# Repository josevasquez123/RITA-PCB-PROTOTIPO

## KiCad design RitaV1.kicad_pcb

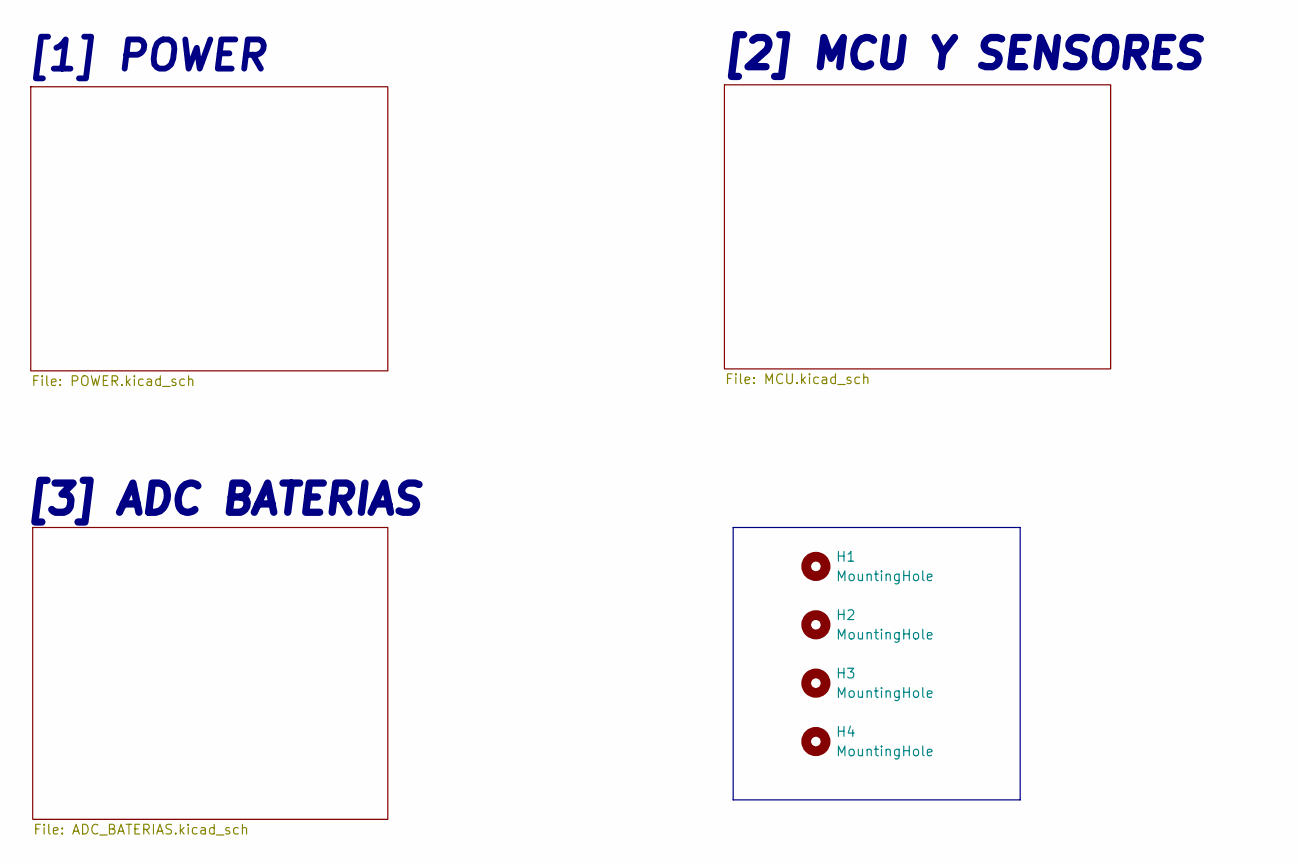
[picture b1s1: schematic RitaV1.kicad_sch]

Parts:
H1, H2, H3, H4: MountingHole; MountingHole_3.2mm_M3

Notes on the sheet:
[1] POWER
[3] ADC BATERIAS
[2] MCU Y SENSORES

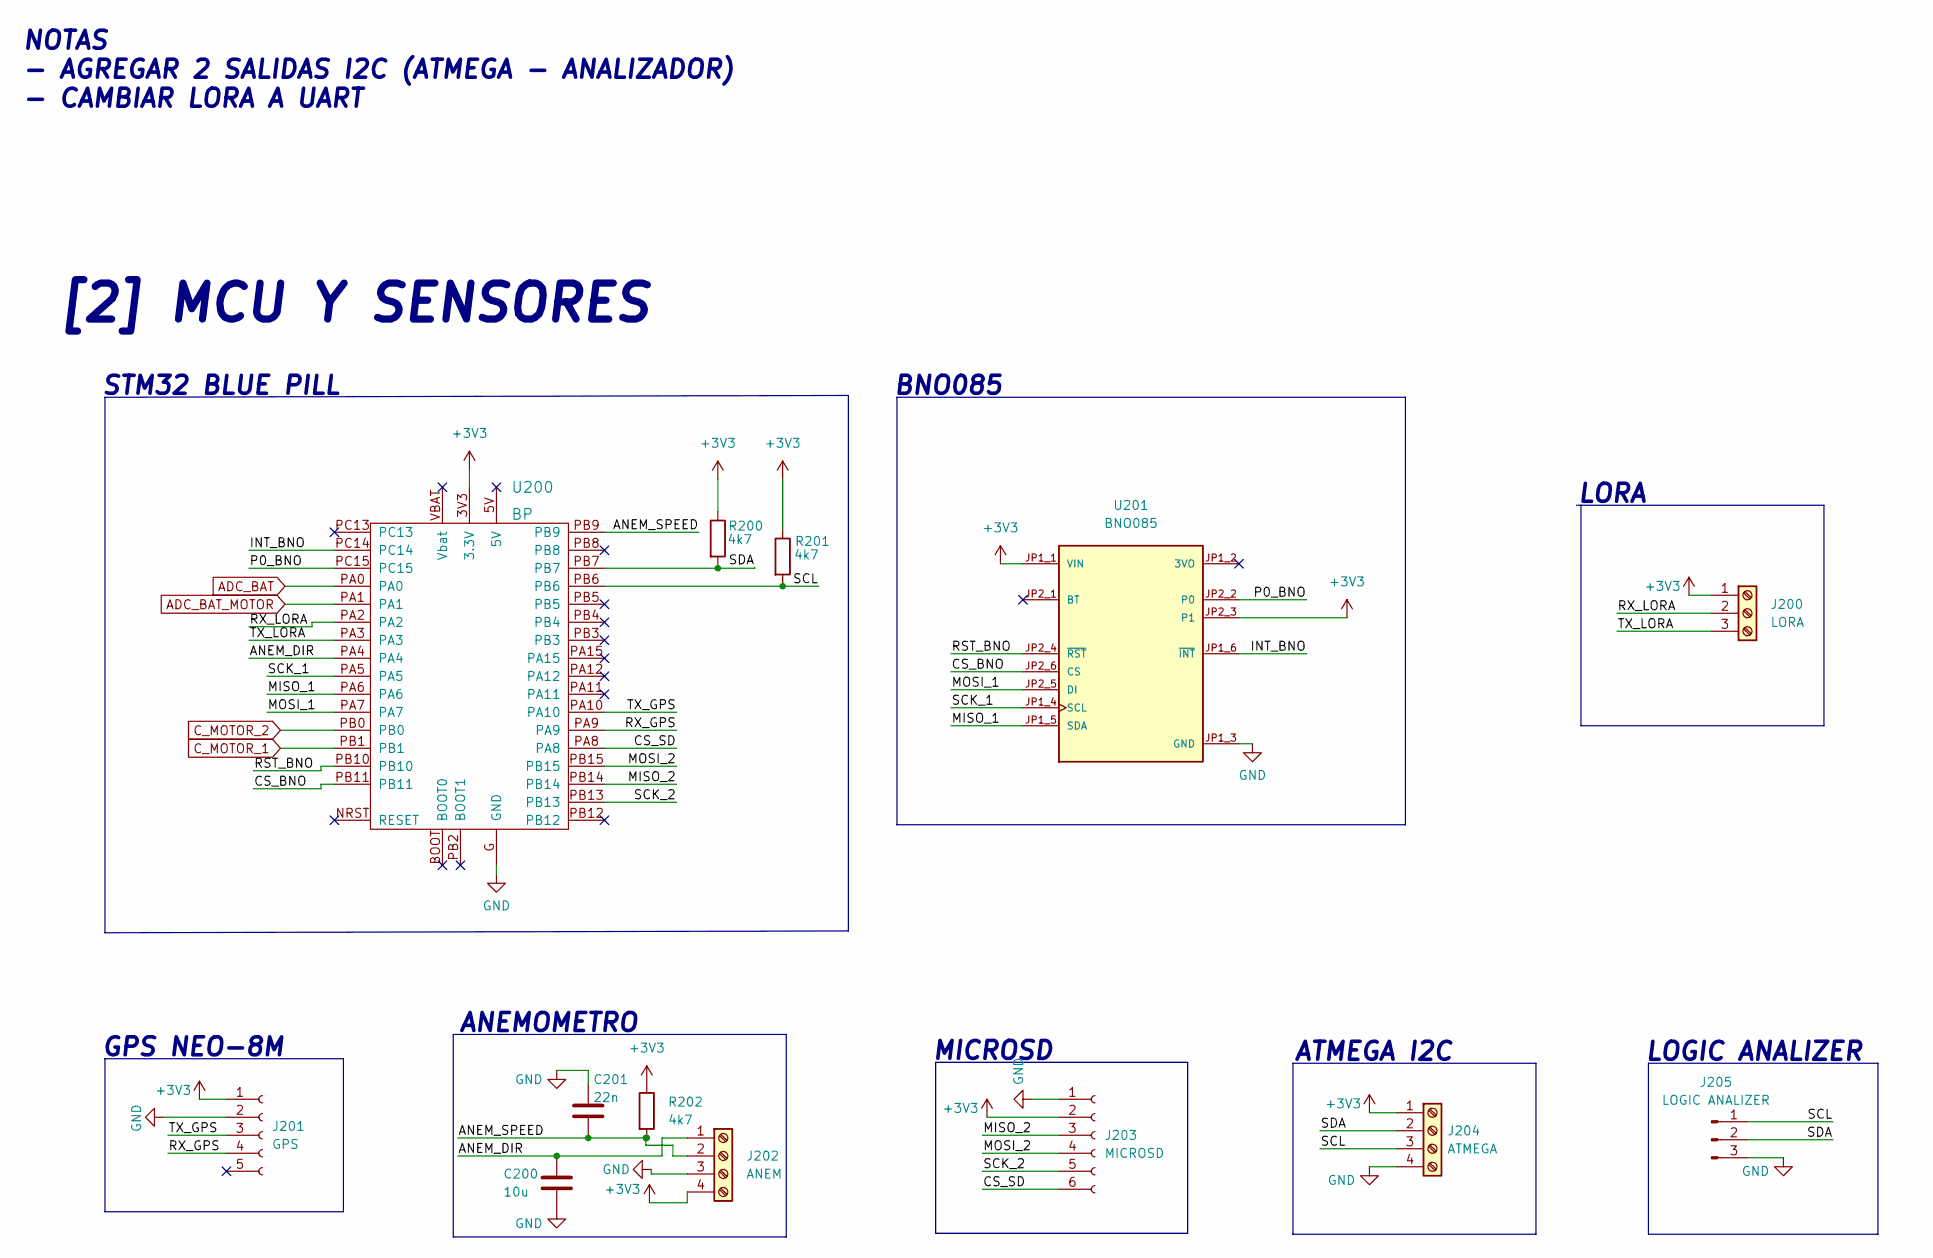
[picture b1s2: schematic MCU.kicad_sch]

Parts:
C200: 10u; C_Radial_D4.0mm_H5.0mm_P1.50mm
C201: 22n; C_Disc_D3.0mm_W1.6mm_P2.50mm
J200: LORA; PhoenixContact_MSTBA_2,5_3-G-5,08_1x03_P5.08mm_Horizontal
J201: GPS; PinSocket_1x05_P2.54mm_Horizontal
J202: ANEM; PhoenixContact_MSTBA_2,5_4-G-5,08_1x04_P5.08mm_Horizontal
J203: MICROSD; PinSocket_1x06_P2.54mm_Horizontal
J204: ATMEGA; PhoenixContact_MSTBA_2,5_4-G-5,08_1x04_P5.08mm_Horizontal
J205: LOGIC ANALIZER; PinHeader_1x03_P2.54mm_Vertical
R200, R201, R202: 4k7; R_Axial_DIN0204_L3.6mm_D1.6mm_P5.08mm_Horizontal
U200: BP; blue_pill
U201: BNO085; MODULE_4754; PARTREV 2021-03-16

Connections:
+3V3: J200.1, J201.1, J202.4, J203.2, J204.1, R200.1, R201.1, R202.1, U200.3V3 (3.3V), U201.JP1_1 (VIN), U201.JP2_3 (P1); also elsewhere on the board
/MCU/ANEM_DIR: C200.1, J202.1, U200.PA4
/MCU/ANEM_SPEED: C201.2, J202.2, R202.2, U200.PB9
/MCU/CS_BNO: U200.PB11, U201.JP2_6 (CS)
/MCU/CS_SD: J203.6, U200.PA8
/MCU/INT_BNO: U200.PC14, U201.JP1_6 (~INT)
/MCU/MISO_1: U200.PA6, U201.JP1_5 (SDA)
/MCU/MISO_2: J203.3, U200.PB14
/MCU/MOSI_1: U200.PA7, U201.JP2_5 (DI)
/MCU/MOSI_2: J203.4, U200.PB15
/MCU/P0_BNO: U200.PC15, U201.JP2_2 (P0)
/MCU/RST_BNO: U200.PB10, U201.JP2_4 (~RST)
/MCU/RX_GPS: J201.4, U200.PA9
/MCU/RX_LORA: J200.2, U200.PA2
/MCU/SCK_1: U200.PA5, U201.JP1_4 (SCL)
/MCU/SCK_2: J203.5, U200.PB13
/MCU/SCL: J204.3, J205.1, R201.2, U200.PB6
/MCU/SDA: J204.2, J205.2, R200.2, U200.PB7
/MCU/TX_GPS: J201.3, U200.PA10
/MCU/TX_LORA: J200.3, U200.PA3
ADC_BAT: U200.PA0; also elsewhere on the board
ADC_BAT_MOTOR: U200.PA1; also elsewhere on the board
C_MOTOR_1: U200.PB1; also elsewhere on the board
C_MOTOR_2: U200.PB0; also elsewhere on the board
GND: C200.2, C201.1, J201.2, J202.3, J203.1, J204.4, J205.3, U200.G (GND), U201.JP1_3 (GND); also elsewhere on the board

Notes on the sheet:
GPS NEO-8M
MICROSD
BNO085
LOGIC ANALIZER
LORA
ATMEGA I2C
STM32 BLUE PILL
[2] MCU Y SENSORES
NOTAS - AGREGAR 2 SALIDAS I2C (ATMEGA - ANALIZADOR) - CAMBIAR LORA A UART
ANEMOMETRO

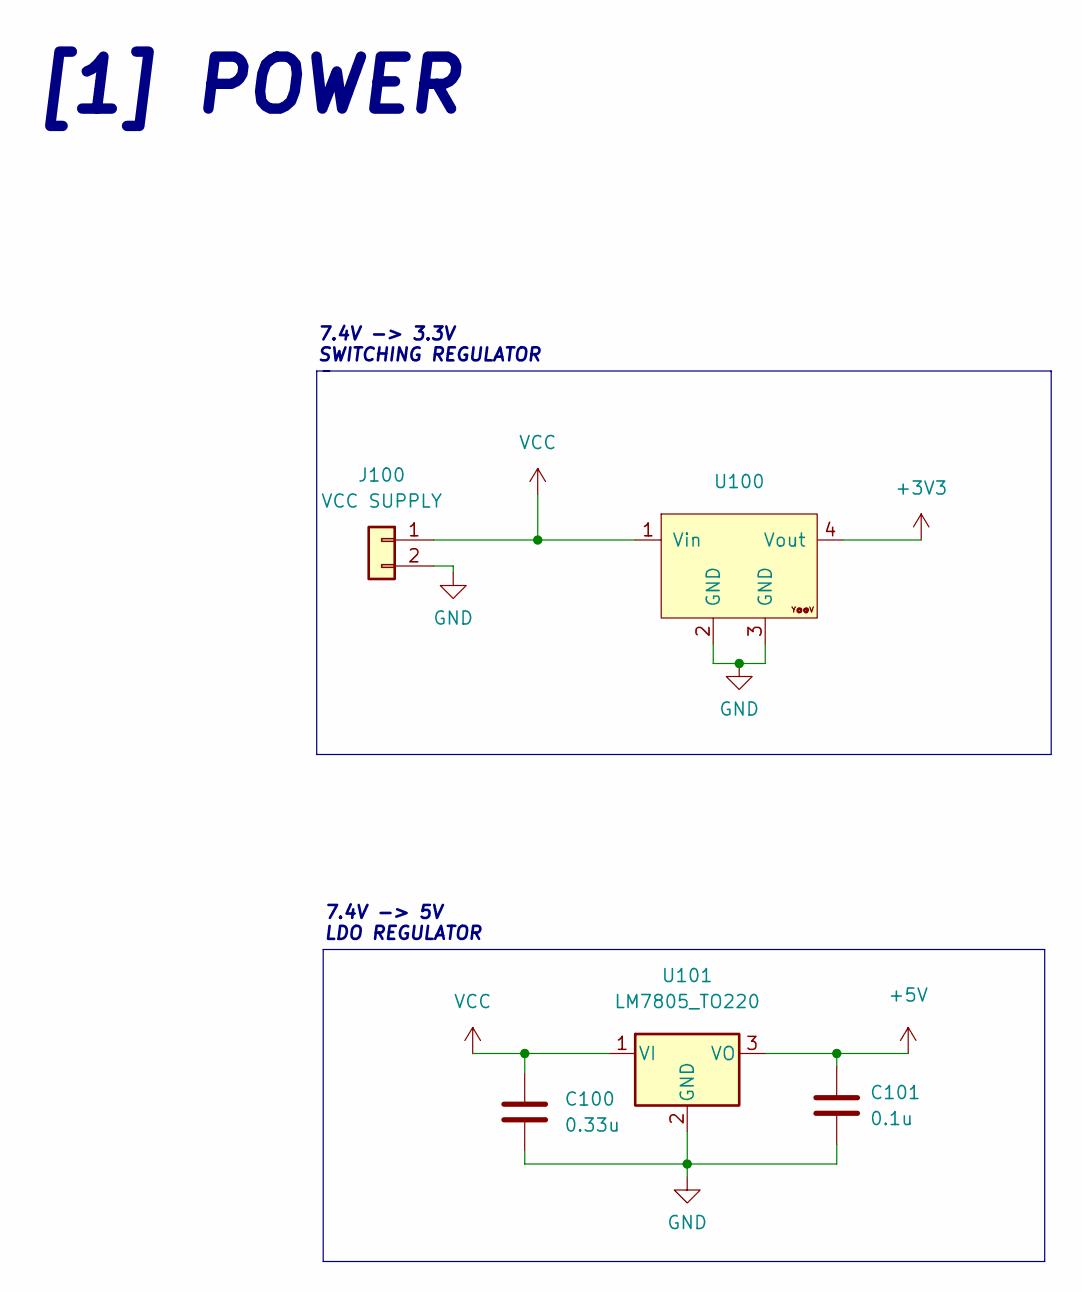
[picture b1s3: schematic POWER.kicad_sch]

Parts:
C100: 0.33u; C_Disc_D3.0mm_W1.6mm_P2.50mm
C101: 0.1u; C_Disc_D3.0mm_W1.6mm_P2.50mm
J100: VCC SUPPLY; PhoenixContact_MSTBA_2,5_2-G-5,08_1x02_P5.08mm_Horizontal
U100: YAAJ_DCDC_StepDown_LM2596
U101: LM7805_TO220; TO-220-3_Vertical

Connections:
+3V3: U100.4 (Vout); also elsewhere on the board
+5V: C101.1, U101.3 (VO); also elsewhere on the board
GND: C100.2, C101.2, J100.2, U100.2 (GND), U100.3 (GND), U101.2 (GND); also elsewhere on the board
VCC: C100.1, J100.1, U100.1 (Vin), U101.1 (VI); also elsewhere on the board

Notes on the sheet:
[1] POWER
7.4V -> 5V LDO REGULATOR
7.4V -> 3.3V SWITCHING REGULATOR

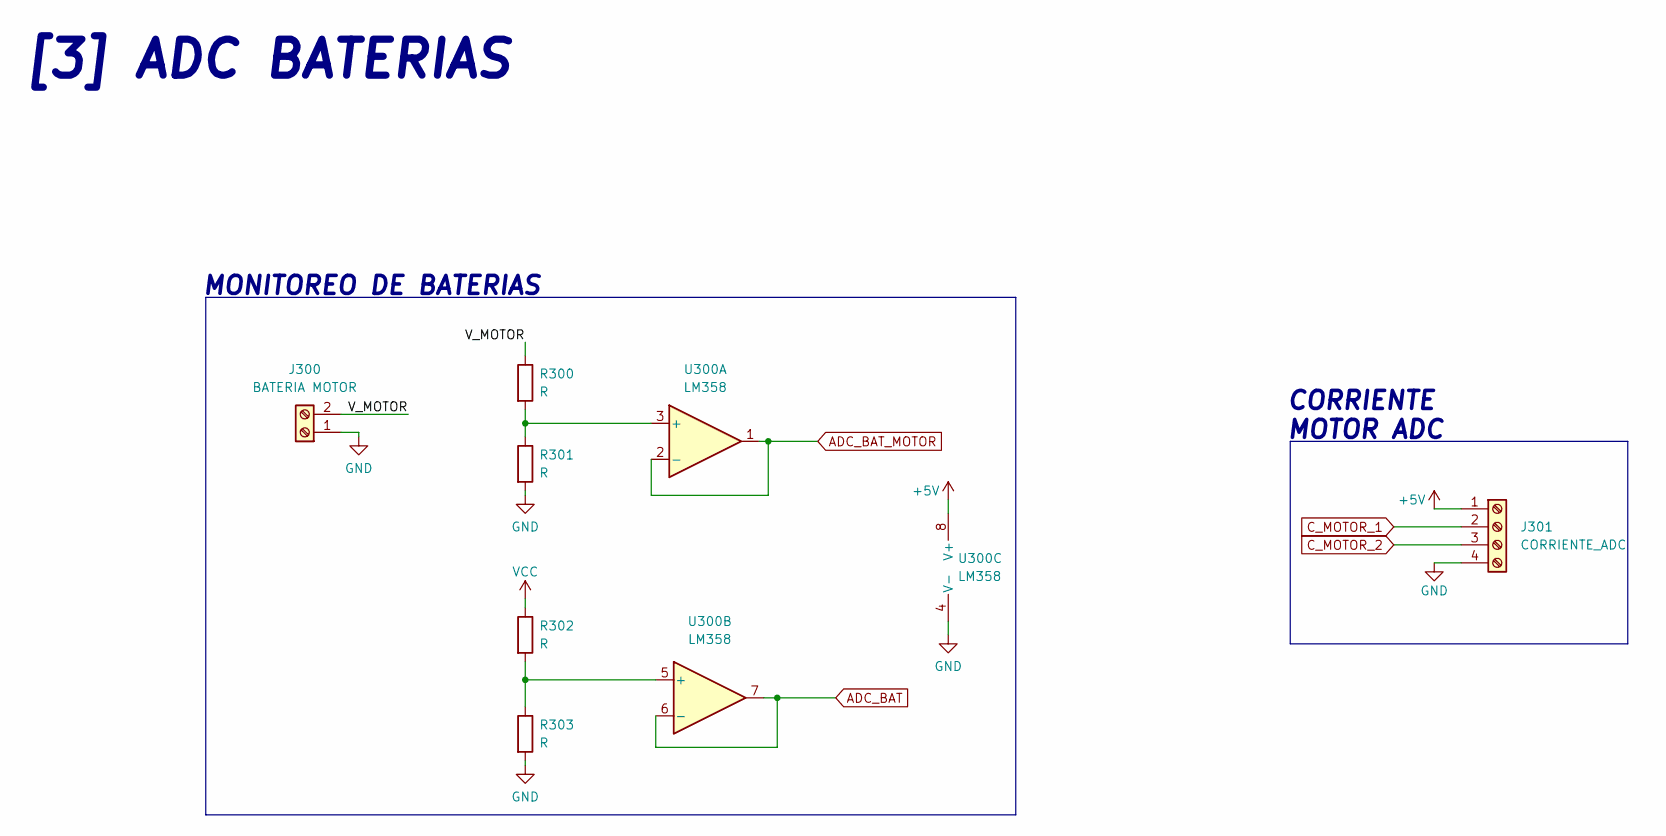
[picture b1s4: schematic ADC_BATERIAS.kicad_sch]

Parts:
J300: BATERIA MOTOR; PhoenixContact_MSTBA_2,5_2-G-5,08_1x02_P5.08mm_Horizontal
J301: CORRIENTE_ADC; PhoenixContact_MSTBA_2,5_4-G-5,08_1x04_P5.08mm_Horizontal
R300, R301, R302, R303: R; R_Axial_DIN0204_L3.6mm_D1.6mm_P5.08mm_Horizontal
U300: LM358; DIP-8_W7.62mm

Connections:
+5V: J301.1, U300.8 (V+); also elsewhere on the board
/ADC_BATERIAS/V_MOTOR: J300.2, R300.1
ADC_BAT: U300.6 (-), U300.7; also elsewhere on the board
ADC_BAT_MOTOR: U300.1, U300.2 (-); also elsewhere on the board
C_MOTOR_1: J301.2; also elsewhere on the board
C_MOTOR_2: J301.3; also elsewhere on the board
GND: J300.1, J301.4, R301.2, R303.2, U300.4 (V-); also elsewhere on the board
unnamed: R300.2, R301.1, U300.3 (+)
unnamed: R302.2, R303.1, U300.5 (+)
VCC: R302.1; also elsewhere on the board

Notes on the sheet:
MONITOREO DE BATERIAS
CORRIENTE MOTOR ADC
[3] ADC BATERIAS

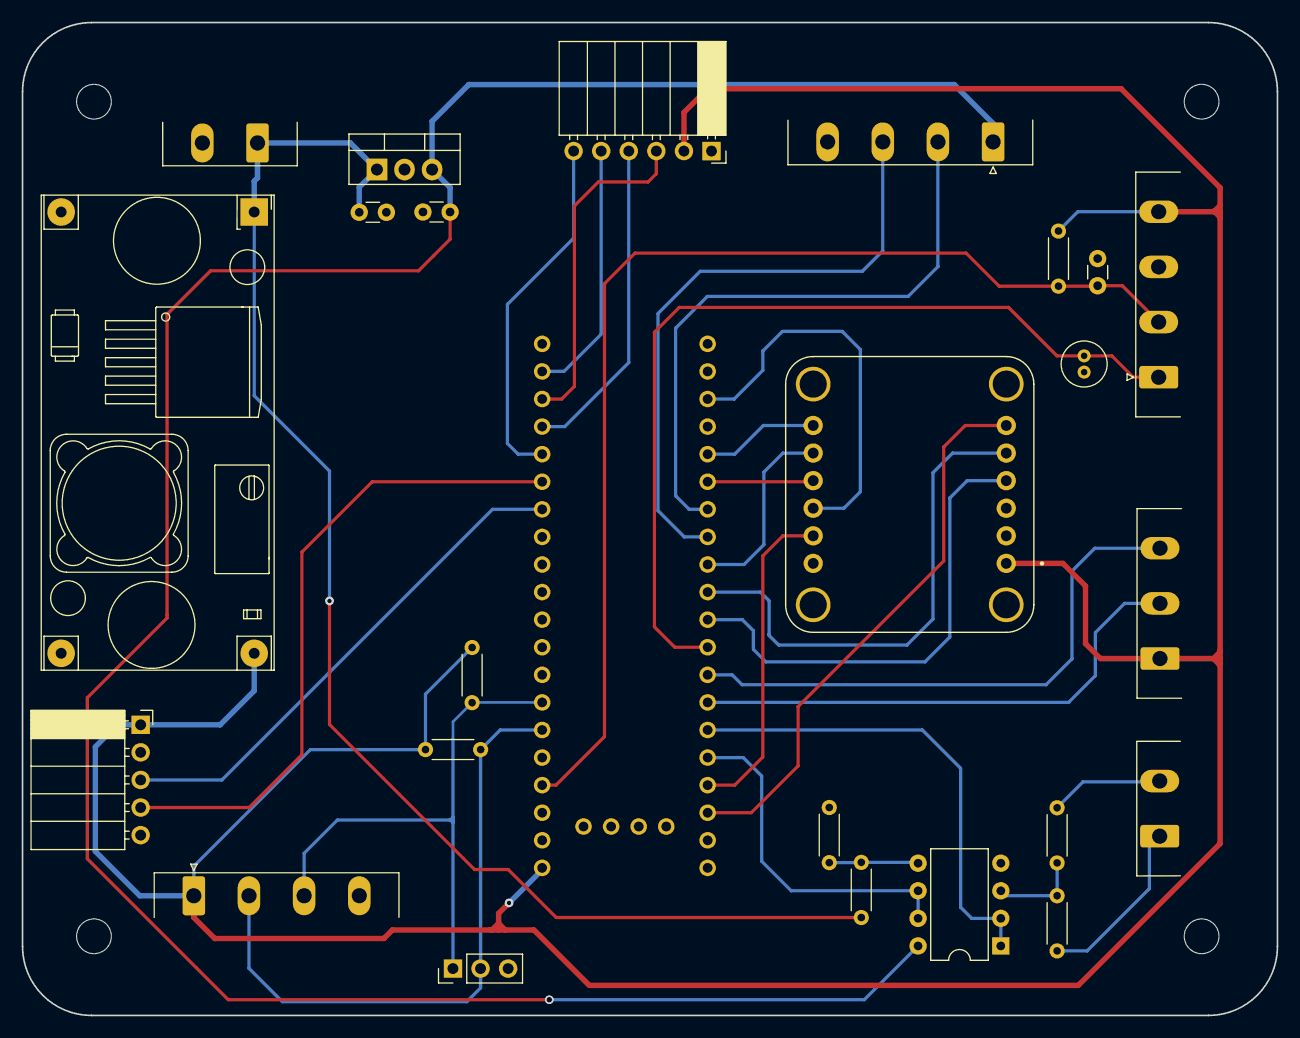
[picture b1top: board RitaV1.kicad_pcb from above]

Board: 2 copper layers, 115.6 x 91.4 mm, 29 parts (0 on the bottom side), 30 nets.

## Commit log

2023-10-14 primera version
2023-11-05 Cambios: Lora comunicacion UART, comunicacion I2C para analizer y Atmega
2023-12-18 last version
